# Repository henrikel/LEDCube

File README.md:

# LEDCube
A 4x4x4 RGB LED cube running on an AVR Atmega 328.

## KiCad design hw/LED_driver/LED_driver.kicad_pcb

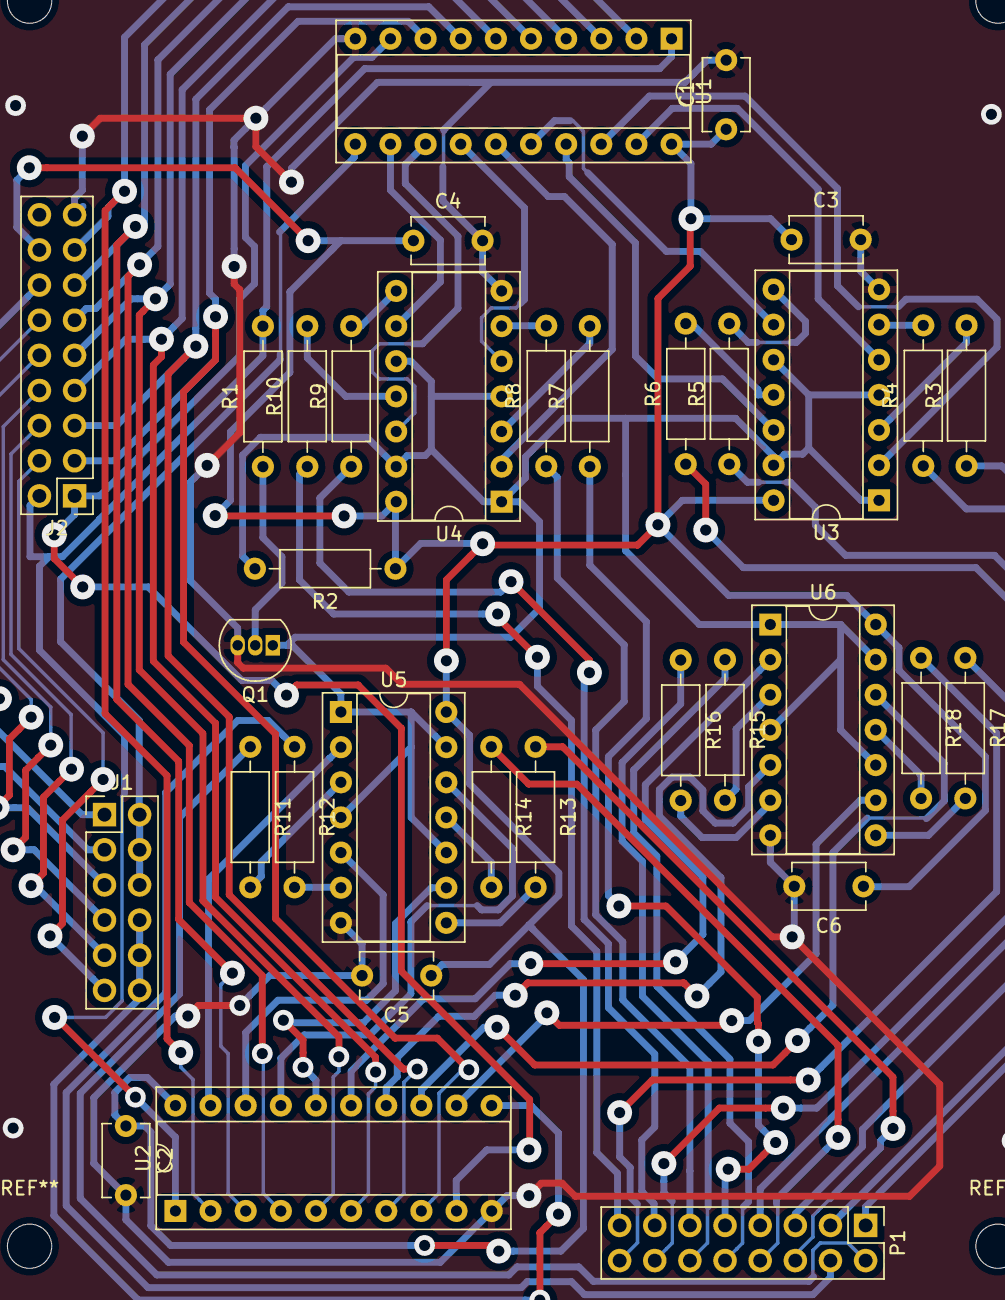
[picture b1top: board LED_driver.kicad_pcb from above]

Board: 2 copper layers, 34 parts (0 on the bottom side), 69 nets.

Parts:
C1, C2, C3, C4, C5, C6: 100n; C_Disc_D5.1mm_W3.2mm_P5.00mm
J1: Conn_02x06_Odd_Even; PinHeader_2x06_P2.54mm_Vertical
J2: Conn_02x09_Odd_Even; PinHeader_2x09_P2.54mm_Vertical
P1: CONN_02X08; PinHeader_2x08_P2.54mm_Vertical
Q1: BC547; TO-92_Inline
R1: 220k; R_Axial_DIN0207_L6.3mm_D2.5mm_P10.16mm_Horizontal
R2: 4k7; R_Axial_DIN0207_L6.3mm_D2.5mm_P10.16mm_Horizontal
R3, R4, R5, R6, R7, R8, R9, R10, R11, R12, R13, R14, R15, R16, R17, R18: 200R; R_Axial_DIN0207_L6.3mm_D2.5mm_P10.16mm_Horizontal
U1, U2: 74HC573; DIP-20_W7.62mm_Socket
U3, U4, U5, U6: 74HC126; DIP-14_W7.62mm_Socket

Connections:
/B1: J1.5, J2.10
/B2: J1.11, J2.4
/D0: J2.15, U1.2, U2.2
/D1: J2.13, U1.3, U2.3
/D2: J2.11, U1.4, U2.4
/D3: J2.9, U1.5, U2.5
/D4: J2.7, U1.6, U2.6
/D5: J2.5, U1.7, U2.7
/D6: J2.3, U1.8, U2.8
/D7: J2.1, U1.9, U2.9
/G1: J1.3, J2.12
/G2: J1.9, J2.6
/OE: J2.2, R1.2, U1.1, U2.1
/R1: J1.1, J2.14
/R2: J1.7, J2.8
Earth: C1.2, C2.2, C3.2, C4.2, C5.2, C6.2, J2.17, Q1.3, U1.10, U2.10, U3.7, U4.7, U5.7, U6.7
unnamed: J1.2, J1.4, J1.6, U1.11
unnamed: J1.8, J1.10, J1.12, U2.11
unnamed: P1.1, R3.1
unnamed: P1.2, R11.1
unnamed: P1.3, R4.1
unnamed: P1.4, R12.1
unnamed: P1.5, R5.1
unnamed: P1.6, R13.1
unnamed: P1.7, R6.1
unnamed: P1.8, R14.1
unnamed: P1.9, R7.1
unnamed: P1.10, R15.1
unnamed: P1.11, R8.1
unnamed: P1.12, R16.1
unnamed: P1.13, R9.1
unnamed: P1.14, R17.1
unnamed: P1.15, R10.1
unnamed: P1.16, R18.1
unnamed: Q1.1, R2.2, U3.1, U3.4, U3.10, U3.13, U4.1, U4.4, U4.10, U4.13, U5.1, U5.4, U5.10, U5.13, U6.1, U6.4, U6.10, U6.13
unnamed: Q1.2, R1.1
unnamed: R3.2, U3.3
unnamed: R4.2, U3.6
unnamed: R5.2, U3.8
unnamed: R6.2, U3.11
unnamed: R7.2, U4.3
unnamed: R8.2, U4.6
unnamed: R9.2, U4.8
unnamed: R10.2, U4.11
unnamed: R11.2, U5.3
unnamed: R12.2, U5.6
unnamed: R13.2, U5.8
unnamed: R14.2, U5.11
unnamed: R15.2, U6.3
unnamed: R16.2, U6.6
unnamed: R17.2, U6.8
unnamed: R18.2, U6.11
unnamed: U1.12, U4.9
unnamed: U1.13, U4.12
unnamed: U1.14, U4.5
unnamed: U1.15, U4.2
unnamed: U1.16, U3.9
unnamed: U1.17, U3.12
unnamed: U1.18, U3.2
unnamed: U1.19, U3.5
unnamed: U2.12, U6.9
unnamed: U2.13, U6.12
unnamed: U2.14, U6.5
unnamed: U2.15, U6.2
unnamed: U2.16, U5.9
unnamed: U2.17, U5.12
unnamed: U2.18, U5.5
unnamed: U2.19, U5.2
VCC: C1.1, C2.1, C3.1, C4.1, C5.1, C6.1, J2.16, R2.1, U1.20, U2.20, U3.14, U4.14, U5.14, U6.14

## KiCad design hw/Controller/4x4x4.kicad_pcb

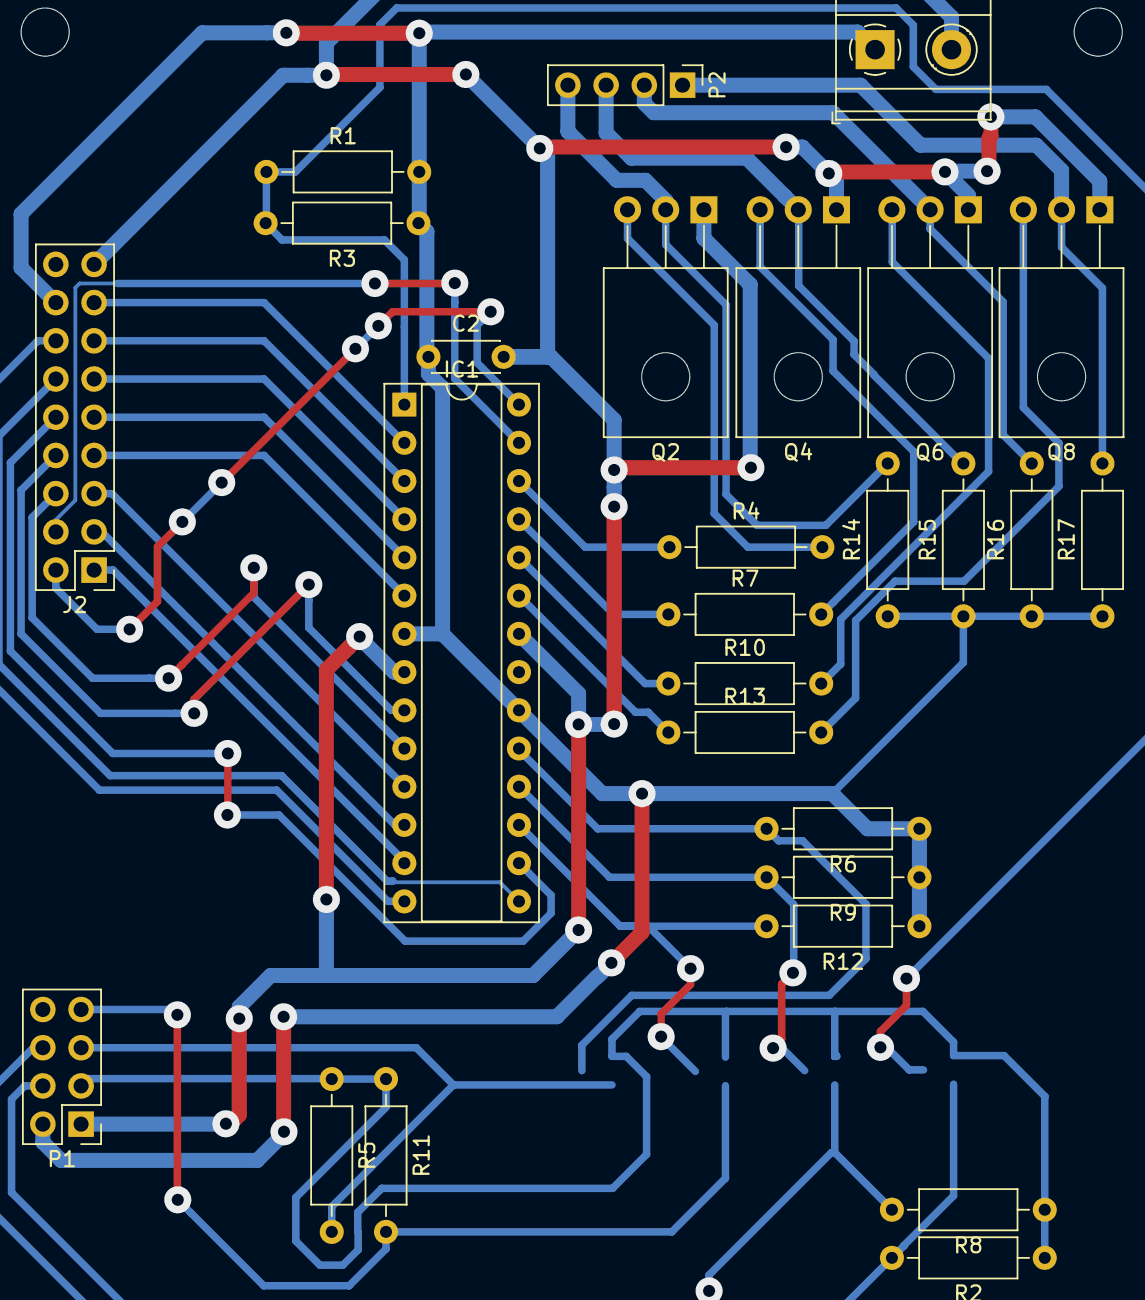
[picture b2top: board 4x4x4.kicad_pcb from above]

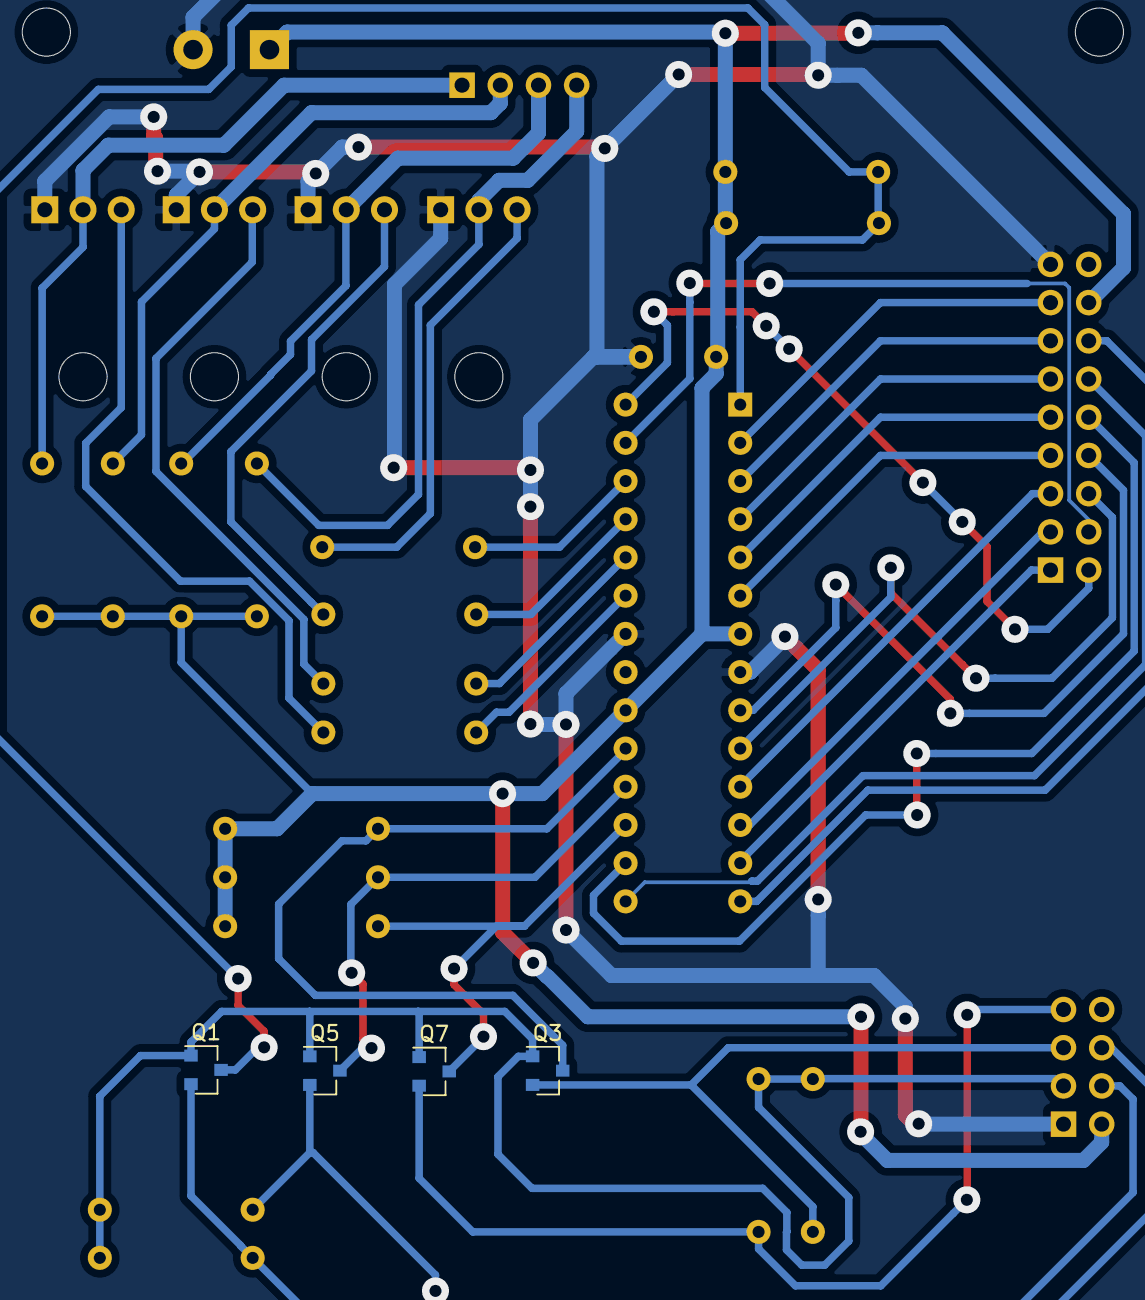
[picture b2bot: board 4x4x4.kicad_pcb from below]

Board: 2 copper layers, 31 parts (4 on the bottom side), 38 nets.

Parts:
C2: 100n; C_Disc_D4.3mm_W1.9mm_P5.00mm
IC1: ATMEGA328-P; DIP-28_W7.62mm_Socket
J1: Screw_Terminal_1x02; TerminalBlock_Phoenix_MKDS-1,5-2-5.08_1x02_P5.08mm_Horizont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
J2: Conn_02x09_Odd_Even; PinHeader_2x09_P2.54mm_Vertical
P1: CONN_01X04; PinHeader_2x04_P2.54mm_Vertical
P2: CONN_01X04; PinHeader_1x04_P2.54mm_Vertical
Q1, Q3, Q5, Q7: BSS138; SOT-23
Q2, Q4, Q6, Q8: BD139; TO-126-3_Horizontal_TabDown
R1, R2, R3, R5, R6, R8, R9, R11, R12, R14, R15, R16, R17: 10k; R_Axial_DIN0207_L6.3mm_D2.5mm_P10.16mm_Horizontal
R4, R7, R10, R13: 220R; R_Axial_DIN0207_L6.3mm_D2.5mm_P10.16mm_Horizontal

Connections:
+3V3: P1.3, Q1.1, Q3.1, Q5.1, Q7.1, R2.1, R5.1, R8.1, R11.1
/B1: IC1.16, J2.10
/B2: IC1.27, J2.4
/D0: IC1.2, J2.15
/D1: IC1.3, J2.13
/D2: IC1.4, J2.11
/D3: IC1.5, J2.9
/D4: IC1.6, J2.7
/D5: IC1.11, J2.5
/D6: IC1.12, J2.3
/D7: IC1.13, J2.1
/G1: IC1.15, J2.12
/G2: IC1.10, J2.6
/Layer0: IC1.23, R13.1
/Layer1: IC1.24, R10.1
/Layer2: IC1.25, R7.1
/Layer3: IC1.26, R4.1
/MISO_PI: P1.6, Q5.2, R8.2
/MOSI_PI: P1.7, Q7.2, R11.2
/OE: IC1.28, J2.2
/R1: IC1.14, J2.14
/R2: IC1.9, J2.8
/RST_PI: P1.4, Q1.2, R2.2
/SCK_PI: P1.5, Q3.2, R5.2
Earth: C2.2, IC1.8, IC1.22, J1.2, J2.17, P1.1, Q2.1, Q4.1, Q6.1, Q8.1
MISO: IC1.18, Q5.3, R9.2
MOSI: IC1.17, Q7.3, R12.2
unnamed: P2.1, Q8.2, R17.2
unnamed: P2.2, Q6.2, R16.2
unnamed: P2.3, Q4.2, R15.2
unnamed: P2.4, Q2.2, R14.2
unnamed: Q2.3, R4.2
unnamed: Q4.3, R7.2
unnamed: Q6.3, R10.2
unnamed: Q8.3, R13.2
RST: IC1.1, Q1.3, R1.1, R3.2
SCK: IC1.19, Q3.3, R6.2
VCC: C2.1, IC1.7, IC1.20, J1.1, J2.16, P1.2, R1.2, R3.1, R6.1, R9.1, R12.1, R14.1, R15.1, R16.1, R17.1

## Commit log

2022-07-25 Add code
2022-07-25 Changed license
2022-08-01 Added schematic images
2022-08-01 Added image of assembled product
